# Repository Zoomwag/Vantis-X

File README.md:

# Vantis-X

Vantis-X is a high-performance fixed-wing UAV with a custom-designed flight controller. The aircraft is designed to be fully 3D-printed, with a focus on lightweight construction and integrating the airframe and electronics into one system.

**Development journal:** [JOURNAL.md](https://github.com/Zoomwag/Vantis-X/blob/main/JOURNAL.md)

The aircraft has a wingspan of approximately 1 metre and an estimated all-up weight of 450 g. The design is still in development, with the airframe and flight controller being developed alongside each other.

## Flight Controller

The flight controller is being designed specifically for Vantis-X rather than using an off-the-shelf board. This includes the schematic, component selection, PCB layout and 3D modelling before manufacture.

**Board overview**

**3D model**

**Schematic**

**PCB layout**

The PCB layout translates the circuit schematic into a physical board, with component placement, routing and grounding all considered during the design.

## Specifications

| Parameter | Value |
|---|---|
| Wingspan | 1 m |
| Estimated all-up weight | 450 g |
| Construction | 3D-printed |
| Aircraft type | Fixed-wing UAV |
| Flight controller | Custom-designed |

## Development

The project is being developed from the initial CAD and electronics designs through to assembly and flight testing. The journal documents the process, including design changes and technical progress.

[View the development journal](https://github.com/Zoomwag/Vantis-X/blob/main/JOURNAL.md)

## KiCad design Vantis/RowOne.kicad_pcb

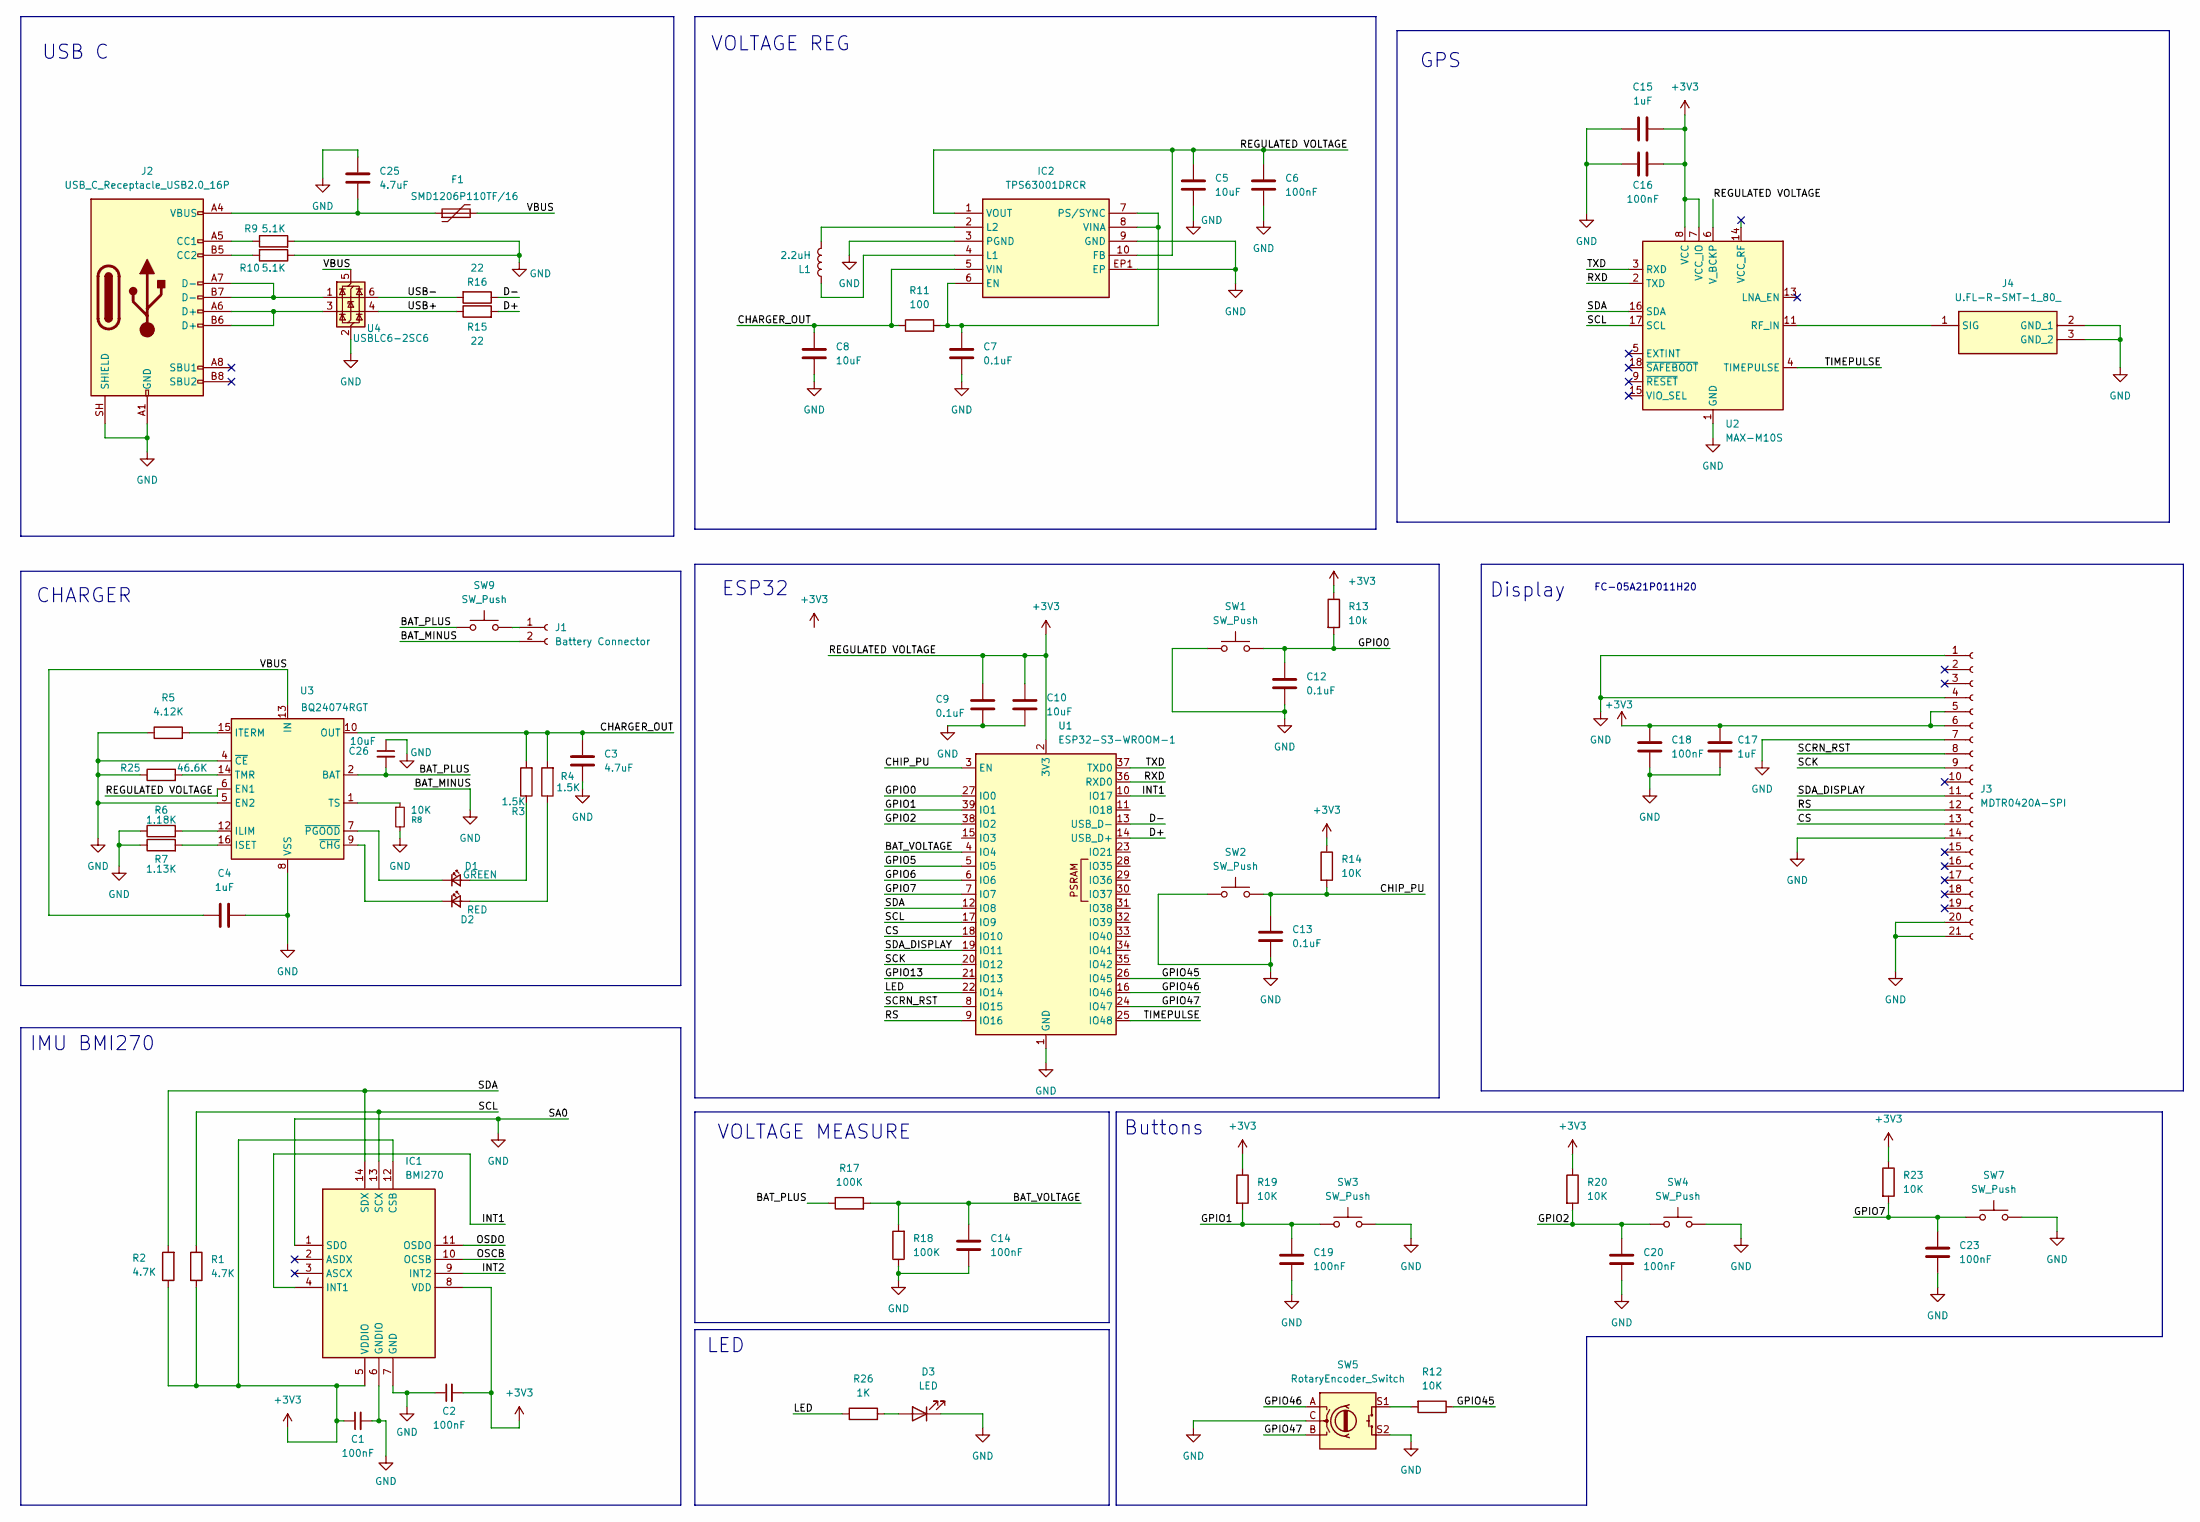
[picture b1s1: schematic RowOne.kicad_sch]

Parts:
C1, C2, C14, C16, C18, C19, C20, C23: 100nF; C_0603_1608Metric
C3, C25: 4.7uF; C_0603_1608Metric
C4, C15, C17: 1uF; C_0603_1608Metric
C5, C8, C10, C26: 10uF; C_0805_2012Metric
C6: 100nF; C_0805_2012Metric
C7, C9, C12, C13: 0.1uF; C_0603_1608Metric
D1: GREEN; LED_0805_2012Metric
D2: RED; LED_0805_2012Metric
D3: LED; LED_0805_2012Metric
F1: SMD1206P110TF/16; Fuse_1206_3216Metric
IC1: BMI270; Mouser Part Number 262-BMI270
IC2: TPS63001DRCR; Mouser Part Number 595-TPS63001DRCR
J1: Battery Connector; JST_PH_S2B-PH-SM4-TB_1x02-1MP_P2.00mm_Horizontal
J2: USB_C_Receptacle_USB2.0_16P; USB_C_Receptacle_HRO_TYPE-C-31-M-12
J3: MDTR0420A-SPI; KH-FG0_5-H2_0-21PIN
J4: U.FL-R-SMT-1_80_; UFLRSMT180; Mouser Part Number 798-UFLRSMT180
L1: 2.2uH; L_0603_1608Metric
R1, R2: 4.7K; R_0603_1608Metric
R3, R4: 1.5K; R_0603_1608Metric
R5: 4.12K; R_0603_1608Metric
R6: 1.18K; R_0603_1608Metric
R7: 1.13K; R_0603_1608Metric
R8, R12, R14, R19, R20, R23: 10K; R_0603_1608Metric
R9, R10: 5.1K; R_0603_1608Metric
R11: 100; R_0603_1608Metric
R13: 10k; R_0603_1608Metric
R15, R16: 22; R_0603_1608Metric
R17, R18: 100K; R_0603_1608Metric
R25: 46.6K; R_0603_1608Metric
R26: 1K; R_0603_1608Metric
SW1, SW2: SW_Push
SW3, SW4, SW7: SW_Push; M22K095111F5
SW5: RotaryEncoder_Switch; ED08902M-SP13_5S6_5-C10-20G
SW9: SW_Push; K3-1391B-51
U1: ESP32-S3-WROOM-1
U2: MAX-M10S; MAX-M10S-00B-01
U3: BQ24074RGT; VQFN-16-1EP_3x3mm_P0.5mm_EP1.6x1.6mm
U4: USBLC6-2SC6; SOT-23-6

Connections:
+3V3: C1.1, C2.2, C5.1, C6.1, C9.1, C10.1, C15.2, C16.2, C17.1, C18.1, IC1.5 (VDDIO), IC1.8 (VDD), IC1.12 (CSB), IC2.1 (VOUT), IC2.10 (FB), J3.5, J3.6, R1.2, R2.1, R13.1, R14.1, R19.1, R20.1, R23.1, U1.2 (3V3), U2.6 (V_BCKP), U2.7 (VCC_IO), U2.8 (VCC), U3.6 (EN1)
/BAT_PLUS: C26.2, R17.1, SW9.1, U3.2 (BAT), U3.3 (BAT)
/BAT_VOLTAGE: C14.1, R17.2, R18.2, U1.4 (IO4)
/CHARGER_OUT: C3.1, C8.1, IC2.5 (VIN), R3.2, R4.2, R11.1, U3.10 (OUT), U3.11 (OUT)
/CHIP_PU: C13.1, R14.2, SW2.2, U1.3 (EN)
/CS: J3.13, U1.18 (IO10)
/D+: R15.2, U1.14 (USB_D+)
/D-: R16.1, U1.13 (USB_D-)
/GPIO0: C12.1, R13.2, SW1.2, U1.27 (IO0)
/GPIO1: C19.1, R19.2, SW3.1, U1.39 (IO1)
/GPIO2: C20.1, R20.2, SW4.1, U1.38 (IO2)
/GPIO5: U1.5 (IO5)
/GPIO6: U1.6 (IO6)
/GPIO7: C23.1, R23.2, SW7.1, U1.7 (IO7)
/GPIO13: U1.21 (IO13)
/GPIO45: R12.1, U1.26 (IO45)
/GPIO46: SW5.A, U1.16 (IO46)
/GPIO47: SW5.B, U1.24 (IO47)
/INT1: IC1.4 (INT1), U1.10 (IO17)
/INT2: IC1.9 (INT2)
/LED: R26.1, U1.22 (IO14)
/OSCB: IC1.10 (OCSB)
/OSDO: IC1.11 (OSDO)
/RS: J3.12, U1.9 (IO16)
/RXD: U1.36 (RXD0), U2.2 (TXD)
/SCK: J3.9, U1.20 (IO12)
/SCL: IC1.13 (SCX), R1.1, U1.17 (IO9), U2.17 (SCL)
/SCRN_RST: J3.8, U1.8 (IO15)
/SDA: IC1.14 (SDX), R2.2, U1.12 (IO8), U2.16 (SDA)
/SDA_DISPLAY: J3.11, U1.19 (IO11)
/TIMEPULSE: U1.25 (IO48), U2.4 (TIMEPULSE)
/TXD: U1.37 (TXD0), U2.3 (RXD)
/USB+: R15.1, U4.4 (I/O2)
/USB-: R16.2, U4.6 (I/O1)
/VBUS: C4.1, F1.2, U3.13 (IN), U4.5 (VBUS)
GND: C1.2, C2.1, C3.2, C4.2, C5.2, C6.2, C7.2, C8.2, C9.2, C10.2, C12.2, C13.2, C14.2, C15.1, C16.1, C17.2, C18.2, C19.2, C20.2, C23.2, C25.1, C26.1, D3.1 (K), IC1.1 (SDO), IC1.6 (GNDIO), IC1.7 (GND), IC2.3 (PGND), IC2.9 (GND), IC2.EP1 (EP), J1.2, J2.A1 (GND), J2.A12 (GND), J2.B1 (GND), J2.B12 (GND), J2.SH (SHIELD), J3.1, J3.4, J3.7, J3.14, J3.20, J3.21, J4.2 (GND_1), J4.3 (GND_2), R5.1, R6.1, R7.1, R8.2, R9.2, R10.1, R18.1, R25.1, SW1.1, SW2.1, SW3.2, SW4.2, SW5.C, SW5.S2, SW7.2, U1.1 (GND), U1.40 (GND), U1.41 (GND), U2.1 (GND), U2.10 (GND), U2.12 (GND), U3.4 (~CE), U3.5 (EN2), U3.8 (VSS), U3.17 (VSS), U4.2 (GND)
unnamed: C25.2, F1.1, J2.A4 (VBUS), J2.A9 (VBUS), J2.B4 (VBUS), J2.B9 (VBUS)
unnamed: D1.2 (A), R3.1
unnamed: D1.1 (K), U3.7 (~PGOOD)
unnamed: D2.2 (A), R4.1
unnamed: D2.1 (K), U3.9 (~CHG)
unnamed: D3.2 (A), R26.2
unnamed: C7.1, IC2.6 (EN), IC2.7 (PS/SYNC), IC2.8 (VINA), R11.2
unnamed: IC2.4 (L1), L1.1
unnamed: IC2.2 (L2), L1.2
unnamed: J1.1, SW9.2
unnamed: J2.A5 (CC1), R9.1
unnamed: J2.B5 (CC2), R10.2
unnamed: J2.A6 (D+), J2.B6 (D+), U4.3 (I/O2)
unnamed: J2.A7 (D-), J2.B7 (D-), U4.1 (I/O1)
unnamed: J4.1 (SIG), U2.11 (RF_IN)
unnamed: R12.2, SW5.S1
unnamed: R6.2, U3.12 (ILIM)
unnamed: R7.2, U3.16 (ISET)
unnamed: R5.2, U3.15 (ITERM)
unnamed: R25.2, U3.14 (TMR)
unnamed: R8.1, U3.1 (TS)

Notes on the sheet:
Display
VOLTAGE REG
Buttons
IMU BMI270
LED
ESP32
GPS
USB C
CHARGER
VOLTAGE MEASURE
FC-05A21P011H20

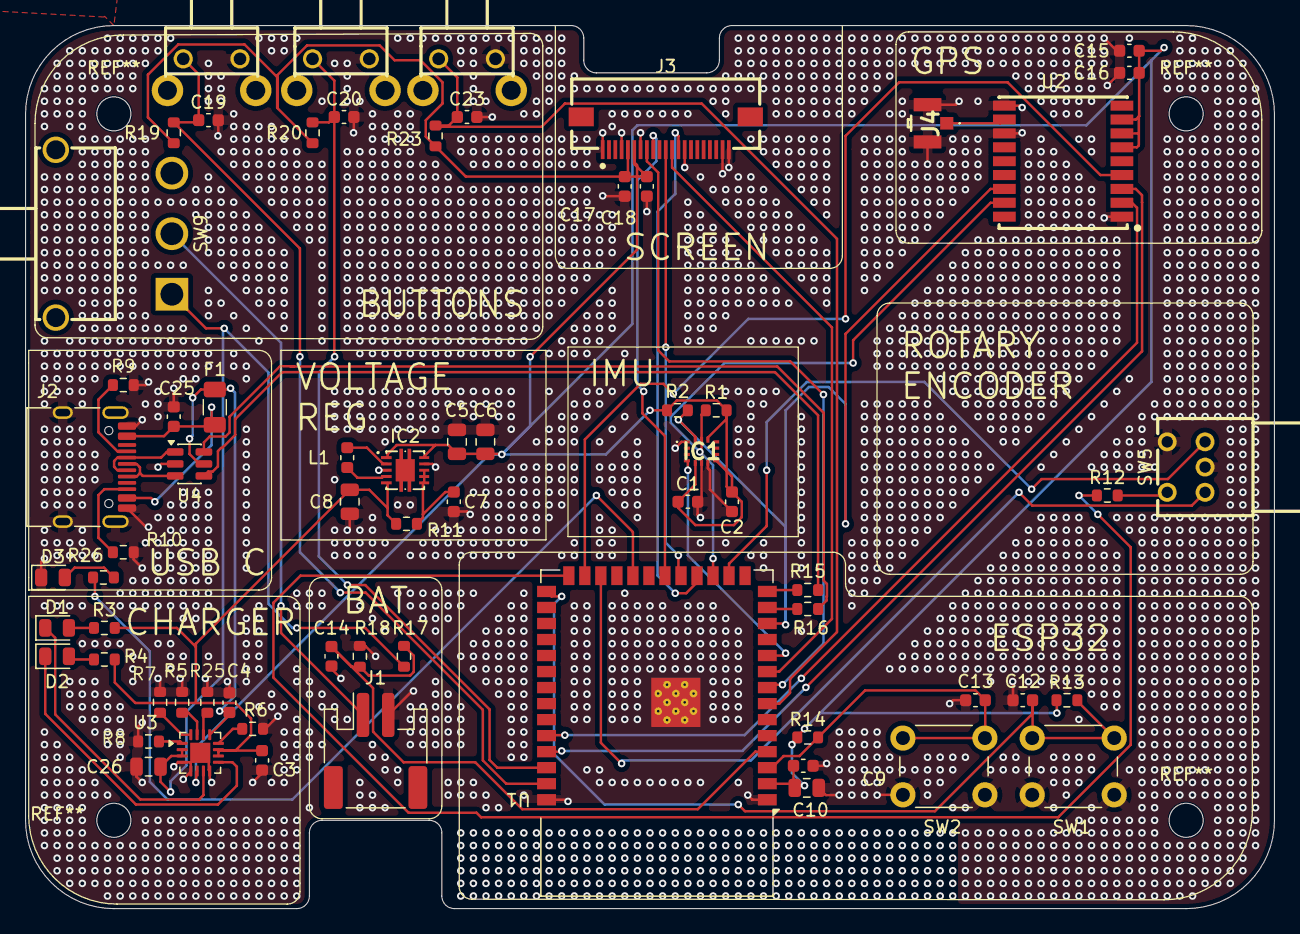
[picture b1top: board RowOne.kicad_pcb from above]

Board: 4 copper layers, 99.0 x 70.0 mm, 67 parts (0 on the bottom side), 51 nets.

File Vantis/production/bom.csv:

Designator,Footprint,Quantity,Value,LCSC Part #
"C1, C14, C16, C18, C19, C2, C20, C23",0603,8,100nF,
"C10, C26, C5, C8",0805,4,10uF,
"C12, C13, C7, C9",0603,4,0.1uF,
"C15, C17, C4",0603,3,1uF,
"C25, C3",0603,2,4.7uF,
C6,0805,1,100nF,
D1,0805,1,GREEN,
D2,0805,1,RED,
D3,0805,1,LED,
F1,1206,1,SMD1206P110TF/16,
IC1,BMI270,1,BMI270,
IC2,TPS63001DRCR,1,TPS63001DRCR,C28060
J1,JST_PH_S2B-PH-SM4-TB_1x02-1MP_P2.00mm_Horizontal,1,Battery Connector,
J2,USB_C_Receptacle_HRO_TYPE-C-31-M-12,1,USB_C_Receptacle_USB2.0_16P,
J3,KH-FG0_5-H2_0-21PIN,1,MDTR0420A-SPI,C2932711
J4,UFLRSMT180,1,U.FL-R-SMT-1_80_,
L1,0603,1,2.2uH,
"R1, R2",0603,2,4.7K,
"R10, R9",0603,2,5.1K,
R11,0603,1,100,
"R12, R13, R14, R19, R20, R23, R8",0603,7,10K,
"R15, R16",0603,2,22,
"R17, R18",0603,2,100K,
R25,0603,1,46.6K,
R26,0603,1,1K,
"R3, R4",0603,2,1.5K,
R5,0603,1,4.12K,
R6,0603,1,1.18K,
R7,0603,1,1.13K,
"SW1, SW2",SW_PUSH_6mm,2,SW_Push,
"SW3, SW4, SW7",M22K095111F5,3,SW_Push,C49393702
SW5,ED08902M-SP13_5S6_5-C10-20G,1,RotaryEncoder_Switch,C18213468
SW9,K3-1391B-51,1,SW_Push,C92656
U1,ESP32-S3-WROOM-1,1,ESP32-S3-WROOM-1,
U2,MAX-M10S-00B-01,1,MAX-M10S,C24834155
U3,VQFN-16-1EP_3x3mm_P0.5mm_EP1.6x1.6mm,1,BQ24074RGT,
U4,SOT-23-6,1,USBLC6-2SC6,
